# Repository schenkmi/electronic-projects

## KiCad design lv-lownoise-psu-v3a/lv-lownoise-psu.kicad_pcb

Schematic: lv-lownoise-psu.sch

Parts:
C1, C2: 100u; CP_Elec_8x6.9
C3, C4: 4.7u; C_1206_3216Metric_Pad1.33x1.80mm_HandSolder
C5, C6: 0.47u; C_0805_2012Metric_Pad1.18x1.45mm_HandSolder
C7, C9: 10u; C_1210_3225Metric_Pad1.33x2.70mm_HandSolder
C8, C10: 330nF; C_0805_2012Metric_Pad1.18x1.45mm_HandSolder
C11, C12: 100nF; C_0805_2012Metric_Pad1.18x1.45mm_HandSolder
C13, C14: 47uF; CP_Elec_6.3x5.8
D1: MB4S; TO-269AA
H1, H2, H3, H4: MountingHole; MountingHole_3.2mm_M3
J1, J3: AC; Pin_D1.3mm_L11.0mm
J2, J5, J8, J10, J11: GND; Pin_D1.3mm_L11.0mm
J4: +15V; Pin_D1.3mm_L11.0mm
J6: -15V; Pin_D1.3mm_L11.0mm
J7: LED; Pin_D1.3mm_L11.0mm
J9: +5V; Pin_D1.3mm_L11.0mm
J12: -5V; Pin_D1.3mm_L11.0mm
Q1: BD679; TO-126-3_Vertical
Q2: BD680; TO-126-3_Vertical
R1, R2: 150k; R_0805_2012Metric_Pad1.20x1.40mm_HandSolder
R3: 240R; R_0805_2012Metric_Pad1.20x1.40mm_HandSolder
R5, R6, R7, R8: 15k; R_0805_2012Metric_Pad1.20x1.40mm_HandSolder
RV1, RV2: 200k; Potentiometer_Bourns_3296W_Vertical
U1: L78L05_SOT89; SOT-89-3
U2: L79L05_SOT89; SOT-89-3
U3: LT3045xMSE; MSOP-12-1EP_3x4mm_P0.65mm_EP1.65x2.85mm
U4: LT3094xMSE; MSOP-12-1EP_3x4mm_P0.65mm_EP1.65x2.85mm

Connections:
GND: C1.2, C2.1, C3.2, C4.1, C5.2, C6.1, C7.1, C8.2, C9.2, C10.1, C11.2, C12.1, C13.2, C14.1, J2.1, J5.1, J8.1, J10.1, J11.1, R1.2, R2.1, R6.2, R7.1, RV1.2, RV1.3, RV2.2, RV2.3, U1.2, U2.1, U3.6 (ILIM), U3.9 (GND), U3.13 (GND), U4.6 (ILIM), U4.9 (GND)
unnamed: C1.1, C8.1, D1.3 (+), Q1.2 (C), R5.1, U1.3
unnamed: C3.1, Q1.1 (E), U3.1 (IN), U3.2 (IN), U3.3 (IN), U3.4 (EN/UV), U3.7 (PGFB)
unnamed: C4.2, Q2.1 (E), U4.1 (IN), U4.2 (IN), U4.3 (EN/UV), U4.5 (PGFB), U4.13 (IN)
unnamed: C5.1, R1.1, RV1.1, U3.8 (SET)
unnamed: C6.2, R2.2, RV2.1, U4.8 (SET)
unnamed: C7.2, J6.1, U4.10 (OUTS), U4.11 (OUT), U4.12 (OUT)
unnamed: C9.1, J4.1, U3.10 (OUTS), U3.11 (OUT), U3.12 (OUT)
unnamed: C2.2, C10.2, D1.4 (-), Q2.2 (C), R8.2, U2.2
unnamed: C11.1, C13.1, J9.1, R3.2, U1.1
unnamed: C12.2, C14.2, J12.1, U2.3
unnamed: D1.1 (~~), J3.1
unnamed: D1.2 (~~), J1.1
unnamed: J7.1, R3.1
unnamed: Q1.3 (B), R5.2, R6.1
unnamed: Q2.3 (B), R7.2, R8.1

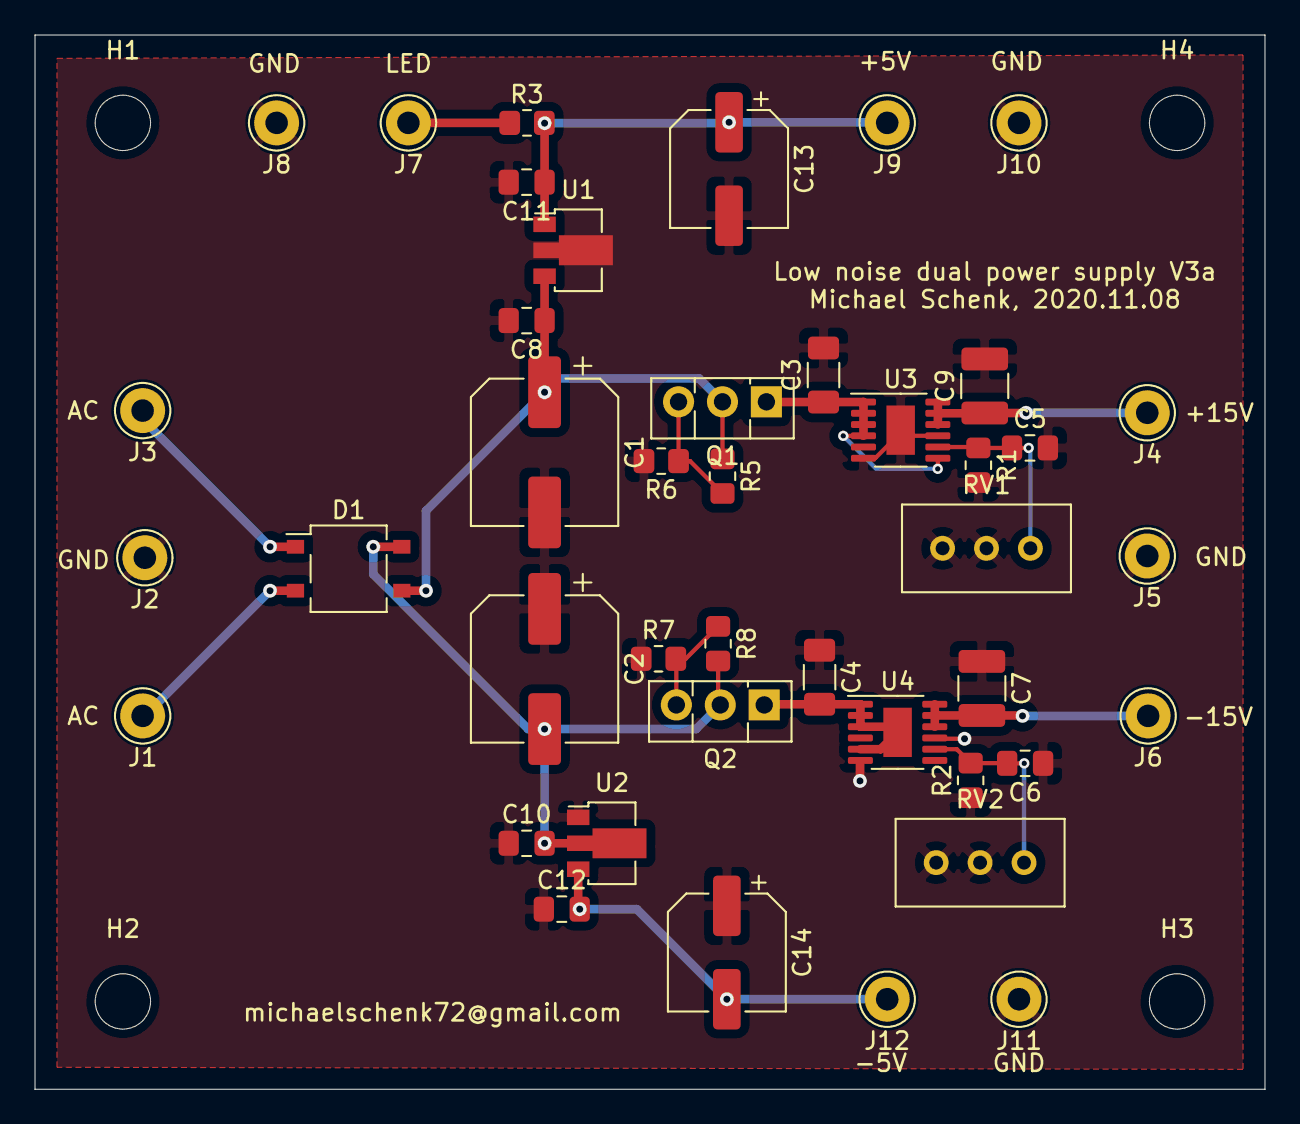
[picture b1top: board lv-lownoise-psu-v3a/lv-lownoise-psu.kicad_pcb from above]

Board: 2 copper layers, 71.1 x 61.0 mm, 46 parts (0 on the bottom side), 16 nets.

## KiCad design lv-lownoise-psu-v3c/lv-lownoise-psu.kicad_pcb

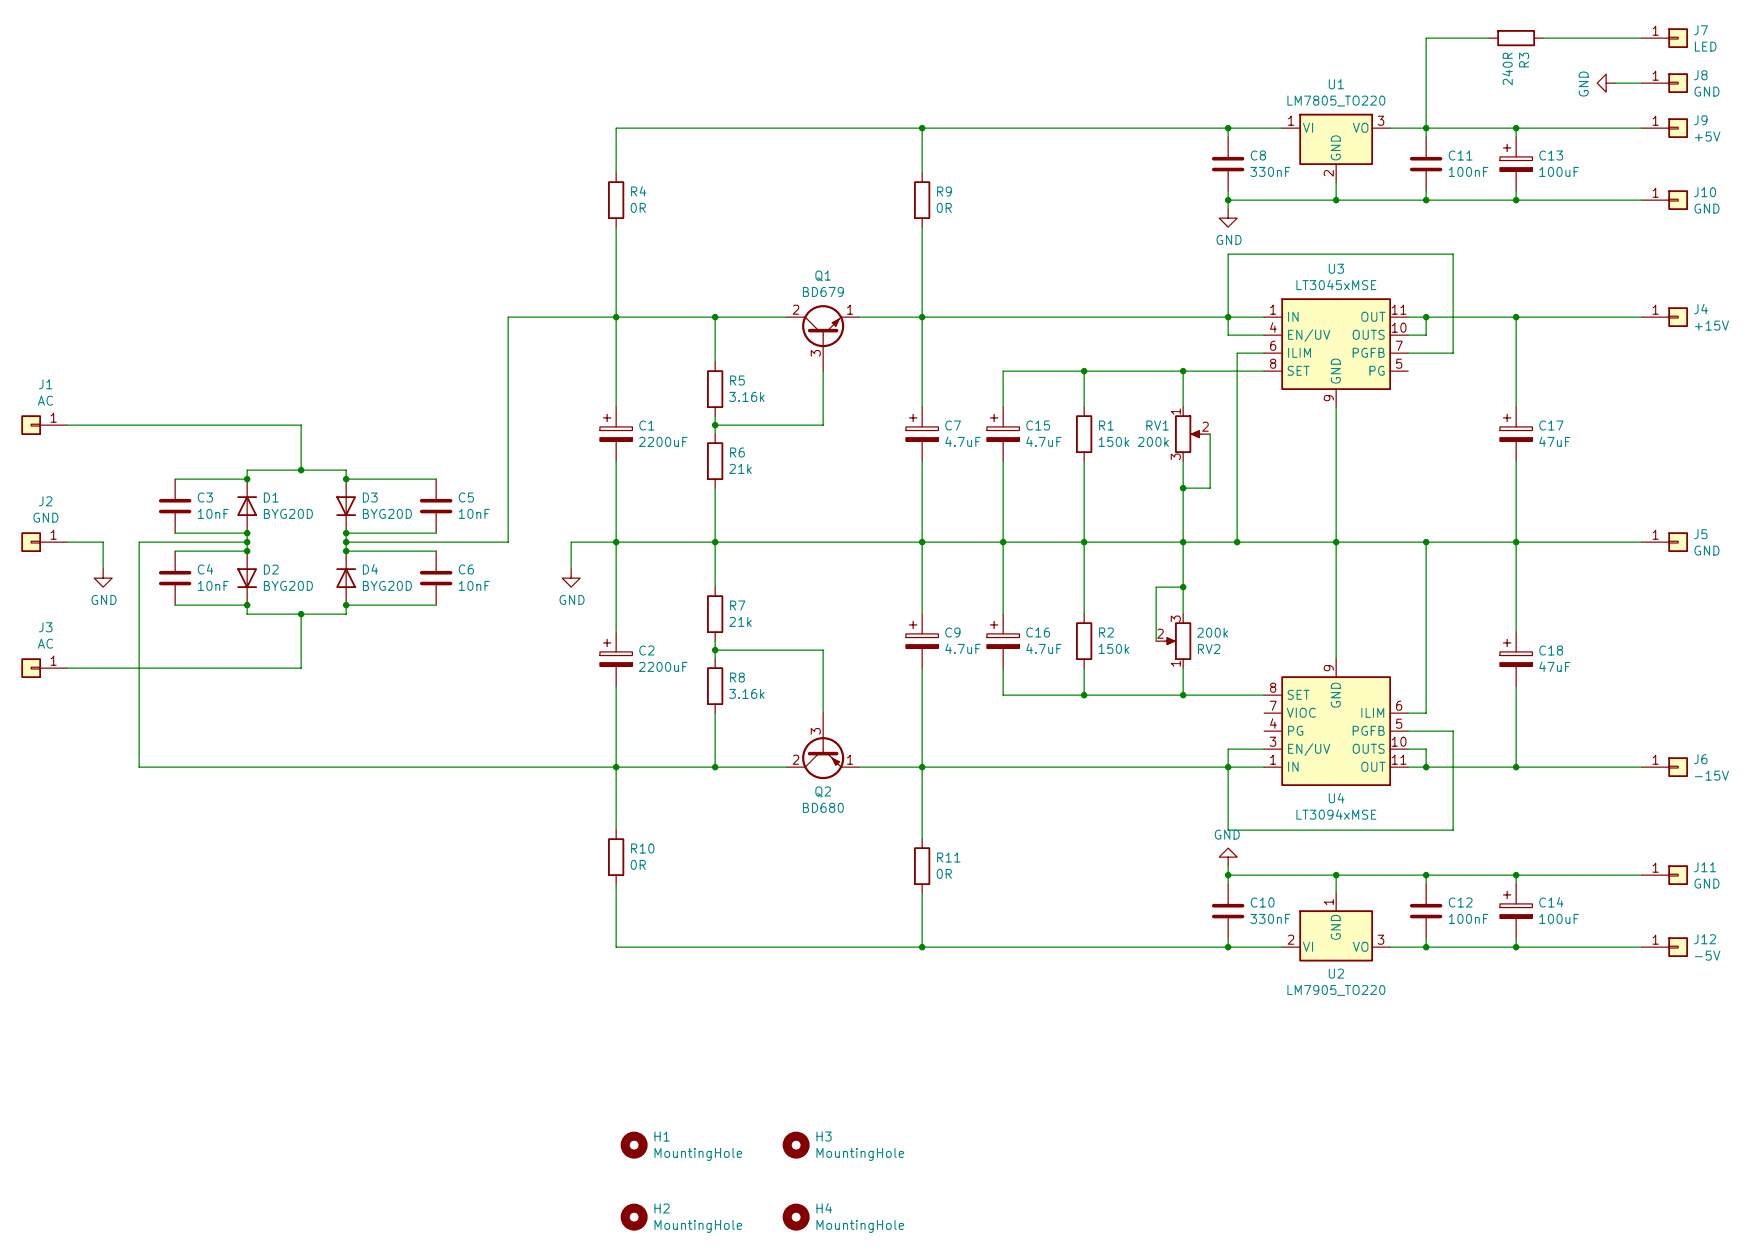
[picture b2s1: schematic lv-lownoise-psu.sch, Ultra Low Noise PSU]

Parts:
C1, C2: 2200uF; CP_Radial_D16.0mm_P7.50mm
C3, C4, C5, C6: 10nF; C_0805_2012Metric_Pad1.18x1.45mm_HandSolder
C7, C9, C15, C16: 4.7uF; CP_EIA-2012-12_Kemet-R_Pad1.30x1.05mm_HandSolder
C8, C10: 330nF; C_0805_2012Metric_Pad1.18x1.45mm_HandSolder
C11, C12: 100nF; C_0805_2012Metric_Pad1.18x1.45mm_HandSolder
C13, C14: 100uF; CP_Radial_D8.0mm_P3.50mm
C17, C18: 47uF; CP_EIA-7343-31_Kemet-D_Pad2.25x2.55mm_HandSolder
D1, D2, D3, D4: BYG20D; D_SMA_Handsoldering
H1, H2, H3, H4: MountingHole; MountingHole_3.2mm_M3
J1, J3: AC; Pin_D1.3mm_L11.0mm
J2, J5, J8, J10, J11: GND; Pin_D1.3mm_L11.0mm
J4: +15V; Pin_D1.3mm_L11.0mm
J6: -15V; Pin_D1.3mm_L11.0mm
J7: LED; Pin_D1.3mm_L11.0mm
J9: +5V; Pin_D1.3mm_L11.0mm
J12: -5V; Pin_D1.3mm_L11.0mm
Q1: BD679; TO-126-3_Vertical
Q2: BD680; TO-126-3_Vertical
R1, R2: 150k; R_0805_2012Metric_Pad1.20x1.40mm_HandSolder
R3: 240R; R_0805_2012Metric_Pad1.20x1.40mm_HandSolder
R4, R9, R10, R11: 0R; R_0805_2012Metric_Pad1.15x1.40mm_HandSolder
R5, R8: 3.16k; R_0805_2012Metric_Pad1.20x1.40mm_HandSolder
R6, R7: 21k; R_0805_2012Metric_Pad1.20x1.40mm_HandSolder
RV1, RV2: 200k; Potentiometer_Bourns_3296W_Vertical
U1: LM7805_TO220; TO-220-3_Vertical
U2: LM7905_TO220; TO-220-3_Vertical
U3: LT3045xMSE; MSOP-12-1EP_3x4mm_P0.65mm_EP1.65x2.85mm
U4: LT3094xMSE; MSOP-12-1EP_3x4mm_P0.65mm_EP1.65x2.85mm

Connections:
GND: C1.2, C2.1, C7.2, C8.2, C9.1, C10.1, C11.2, C12.1, C13.2, C14.1, C15.2, C16.1, C17.2, C18.1, J2.1, J5.1, J8.1, J10.1, J11.1, R1.2, R2.1, R6.2, R7.1, RV1.2, RV1.3, RV2.2, RV2.3, U1.2 (GND), U2.1 (GND), U3.6 (ILIM), U3.9 (GND), U3.13 (GND), U4.6 (ILIM), U4.9 (GND)
unnamed: C1.1, C5.2, C6.1, D3.1 (K), D4.1 (K), Q1.2 (C), R4.2, R5.1
unnamed: C2.2, C3.2, C4.1, D1.2 (A), D2.2 (A), Q2.2 (C), R8.2, R10.1
unnamed: C3.1, C5.1, D1.1 (K), D3.2 (A), J1.1
unnamed: C4.2, C6.2, D2.1 (K), D4.2 (A), J3.1
unnamed: C7.1, Q1.1 (E), R9.2, U3.1 (IN), U3.2 (IN), U3.3 (IN), U3.4 (EN/UV), U3.7 (PGFB)
unnamed: C8.1, R4.1, R9.1, U1.1 (VI)
unnamed: C9.2, Q2.1 (E), R11.1, U4.1 (IN), U4.2 (IN), U4.3 (EN/UV), U4.5 (PGFB), U4.13 (IN)
unnamed: C10.2, R10.2, R11.2, U2.2 (VI)
unnamed: C11.1, C13.1, J9.1, R3.2, U1.3 (VO)
unnamed: C12.2, C14.2, J12.1, U2.3 (VO)
unnamed: C15.1, R1.1, RV1.1, U3.8 (SET)
unnamed: C16.2, R2.2, RV2.1, U4.8 (SET)
unnamed: C17.1, J4.1, U3.10 (OUTS), U3.11 (OUT), U3.12 (OUT)
unnamed: C18.2, J6.1, U4.10 (OUTS), U4.11 (OUT), U4.12 (OUT)
unnamed: J7.1, R3.1
unnamed: Q1.3 (B), R5.2, R6.1
unnamed: Q2.3 (B), R7.2, R8.1

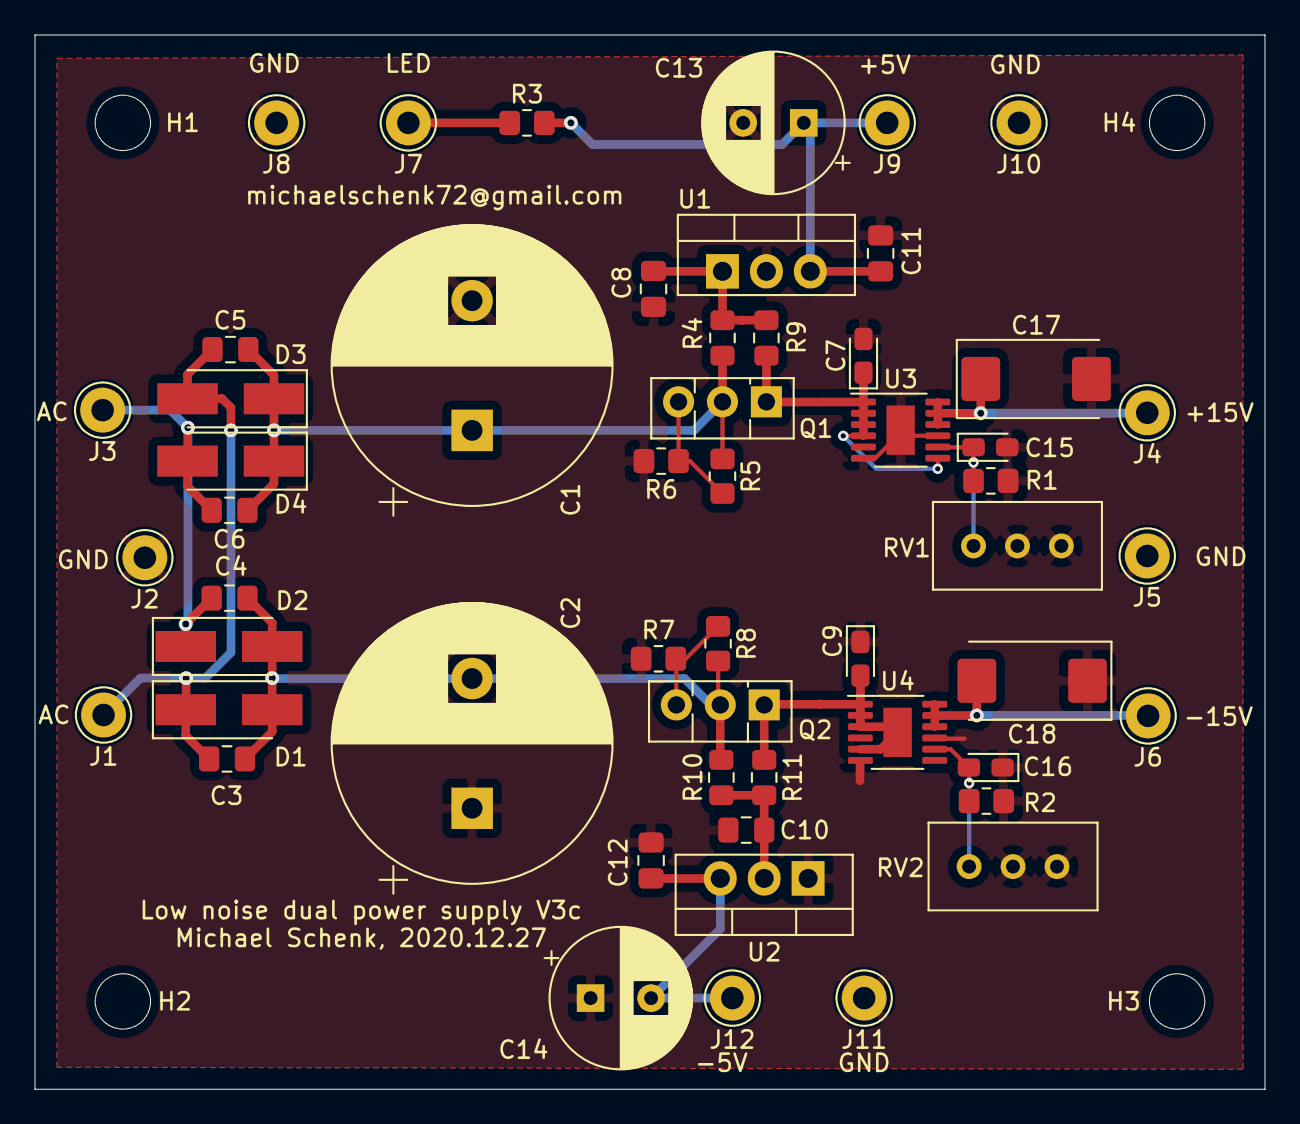
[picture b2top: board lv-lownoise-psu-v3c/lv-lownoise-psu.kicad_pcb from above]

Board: 2 copper layers, 71.1 x 61.0 mm, 57 parts (0 on the bottom side), 18 nets.

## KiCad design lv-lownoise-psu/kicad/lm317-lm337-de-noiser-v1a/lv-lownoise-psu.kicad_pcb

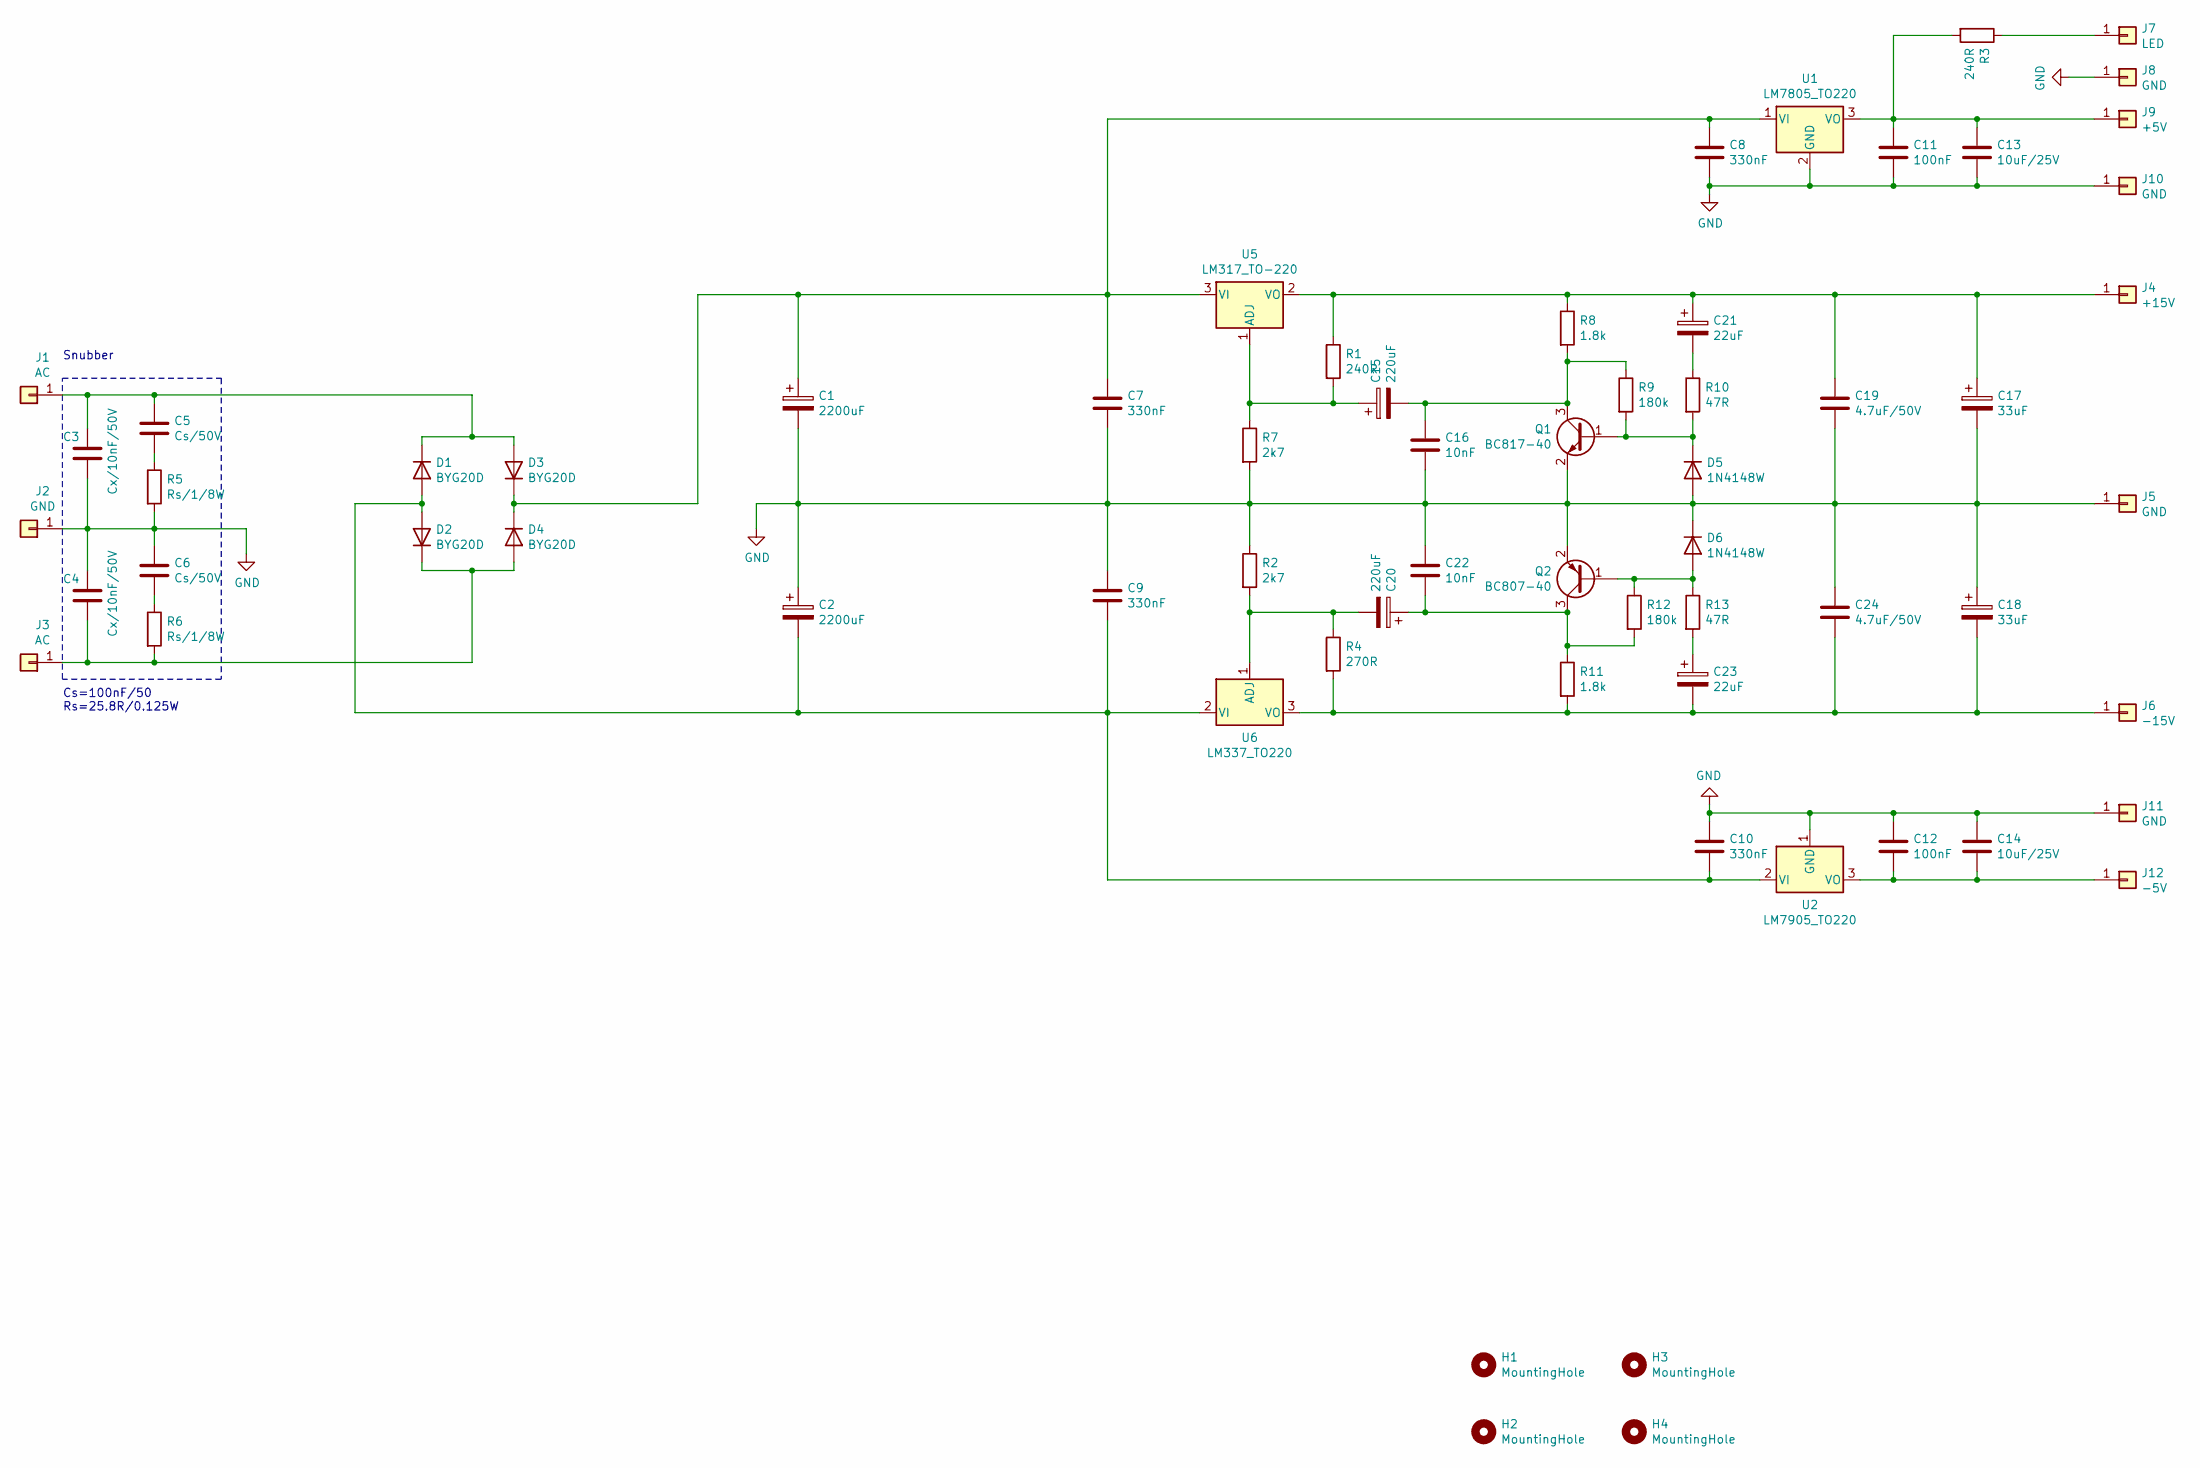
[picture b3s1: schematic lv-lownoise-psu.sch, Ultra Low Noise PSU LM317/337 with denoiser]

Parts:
C1, C2: 2200uF; CP_Radial_D16.0mm_P7.50mm
C3, C4: Cx/10nF/50V; C_0805_2012Metric_Pad1.18x1.45mm_HandSolder
C5, C6: Cs/50V; C_0805_2012Metric_Pad1.18x1.45mm_HandSolder
C7, C8, C9, C10: 330nF; C_0805_2012Metric_Pad1.18x1.45mm_HandSolder
C11, C12: 100nF; C_0805_2012Metric_Pad1.18x1.45mm_HandSolder
C13, C14: 10uF/25V; C_1206_3216Metric_Pad1.33x1.80mm_HandSolder
C15, C20: 220uF; CP_Radial_D8.0mm_P5.00mm
C16, C22: 10nF; C_0805_2012Metric_Pad1.18x1.45mm_HandSolder
C17, C18: 33uF; CP_EIA-7343-31_Kemet-D_Pad2.25x2.55mm_HandSolder
C19, C24: 4.7uF/50V; C_1206_3216Metric_Pad1.33x1.80mm_HandSolder
C21, C23: 22uF; CP_Radial_D5.0mm_P2.50mm
D1, D2, D3, D4: BYG20D; D_SMA_Handsoldering
D5, D6: 1N4148W; D_SOD-123
H1, H2, H3, H4: MountingHole; MountingHole_3.2mm_M3
J1, J3: AC; Pin_D1.3mm_L11.0mm
J2: GND; Pin_D1.3mm_L11.0mm
J4: +15V; Pin_D1.0mm_L10.0mm
J5, J8, J10, J11: GND; Pin_D1.0mm_L10.0mm
J6: -15V; Pin_D1.0mm_L10.0mm
J7: LED; Pin_D1.0mm_L10.0mm
J9: +5V; Pin_D1.0mm_L10.0mm
J12: -5V; Pin_D1.0mm_L10.0mm
Q1: BC817-40; SOT-23
Q2: BC807-40; SOT-23
R1, R3: 240R; R_0805_2012Metric_Pad1.20x1.40mm_HandSolder
R2, R7: 2k7; R_0805_2012Metric_Pad1.20x1.40mm_HandSolder
R4: 270R; R_0805_2012Metric_Pad1.20x1.40mm_HandSolder
R5, R6: Rs/1/8W; R_0805_2012Metric_Pad1.20x1.40mm_HandSolder
R8, R11: 1.8k; R_0805_2012Metric_Pad1.20x1.40mm_HandSolder
R9, R12: 180k; R_0805_2012Metric_Pad1.20x1.40mm_HandSolder
R10, R13: 47R; R_0805_2012Metric_Pad1.20x1.40mm_HandSolder
U1: LM7805_TO220; TO-220-3_Vertical
U2: LM7905_TO220; TO-220-3_Vertical
U5: LM317_TO-220; TO-220-3_Vertical
U6: LM337_TO220; TO-220-3_Vertical

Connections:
GND: C1.2, C2.1, C3.2, C4.1, C6.1, C7.2, C8.2, C9.1, C10.1, C11.2, C12.1, C13.2, C14.1, C16.2, C17.2, C18.1, C19.2, C22.1, C24.1, D5.2 (A), D6.1 (K), J2.1, J5.1, J8.1, J10.1, J11.1, Q1.2 (E), Q2.2 (E), R2.1, R5.2, R7.2, U1.2 (GND), U2.1 (GND)
unnamed: C1.1, C7.1, C8.1, D3.1 (K), D4.1 (K), U1.1 (VI), U5.3 (VI)
unnamed: C3.1, C5.1, D1.1 (K), D3.2 (A), J1.1
unnamed: C4.2, D2.1 (K), D4.2 (A), J3.1, R6.2
unnamed: C5.2, R5.1
unnamed: C6.2, R6.1
unnamed: C2.2, C9.2, C10.2, D1.2 (A), D2.2 (A), U2.2 (VI), U6.2 (VI)
unnamed: C11.1, C13.1, J9.1, R3.2, U1.3 (VO)
unnamed: C12.2, C14.2, J12.1, U2.3 (VO)
unnamed: C15.1, R1.2, R7.1, U5.1 (ADJ)
unnamed: C15.2, C16.1, Q1.3 (C), R8.2, R9.1
unnamed: C17.1, C19.1, C21.1, J4.1, R1.1, R8.1, U5.2 (VO)
unnamed: C18.2, C23.2, C24.2, J6.1, R4.2, R11.2, U6.3 (VO)
unnamed: C20.1, C22.2, Q2.3 (C), R11.1, R12.2
unnamed: C20.2, R2.2, R4.1, U6.1 (ADJ)
unnamed: C21.2, R10.1
unnamed: C23.1, R13.2
unnamed: D5.1 (K), Q1.1 (B), R9.2, R10.2
unnamed: D6.2 (A), Q2.1 (B), R12.1, R13.1
unnamed: J7.1, R3.1

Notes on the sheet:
Snubber
Cs=100nF/50 Rs=25.8R/0.125W

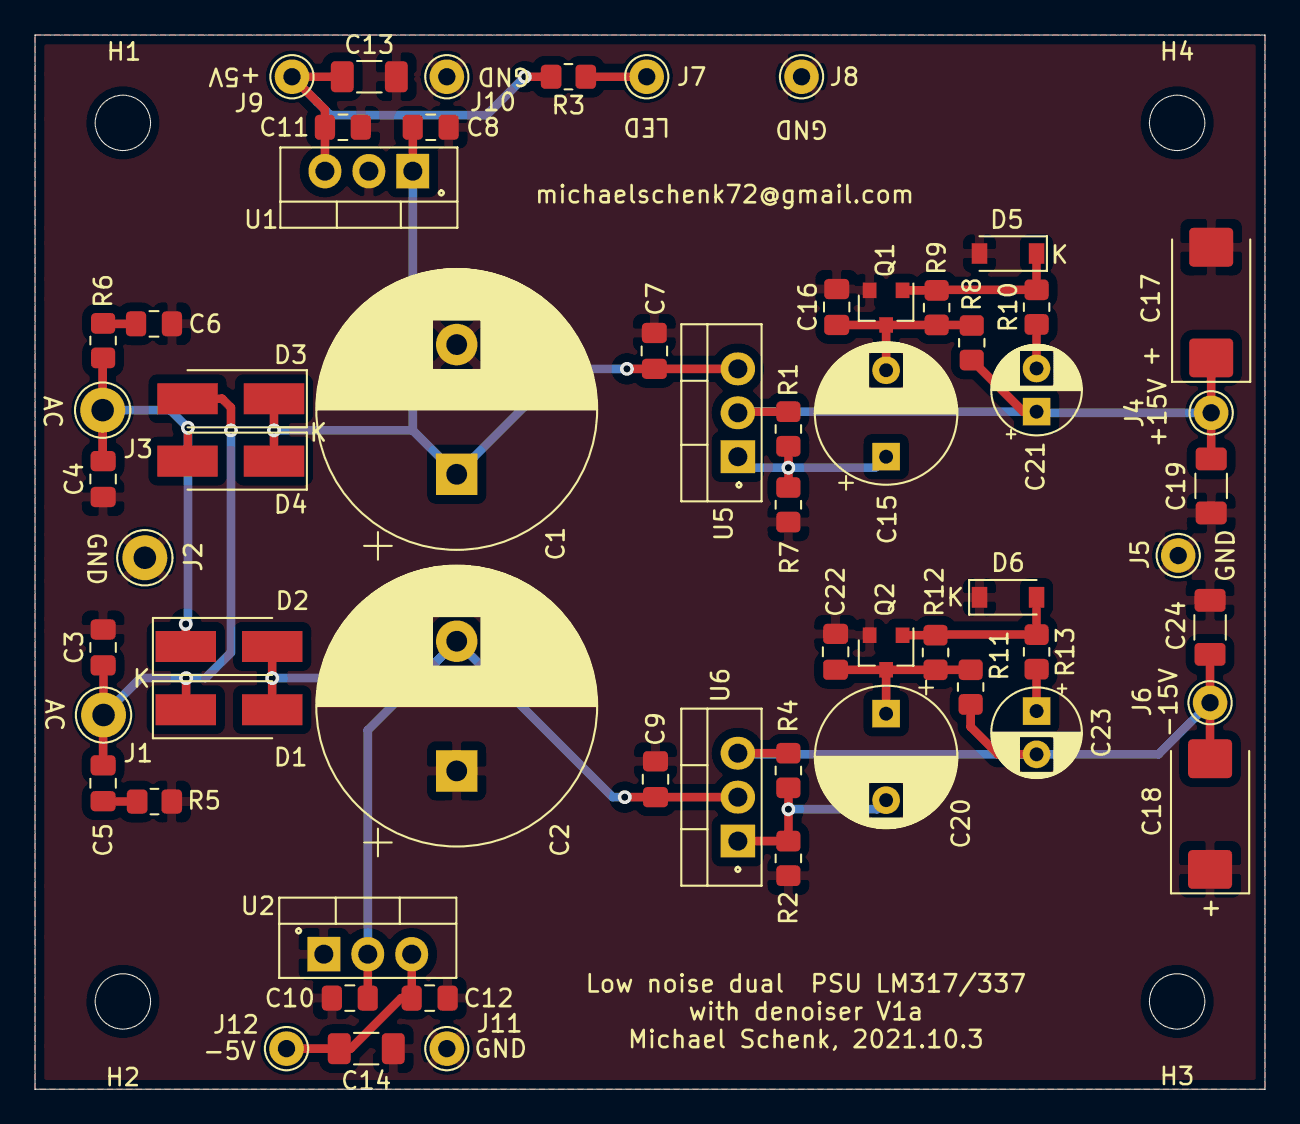
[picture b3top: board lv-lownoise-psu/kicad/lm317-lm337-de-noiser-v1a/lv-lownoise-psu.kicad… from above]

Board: 2 copper layers, 71.1 x 61.0 mm, 65 parts (0 on the bottom side), 20 nets.

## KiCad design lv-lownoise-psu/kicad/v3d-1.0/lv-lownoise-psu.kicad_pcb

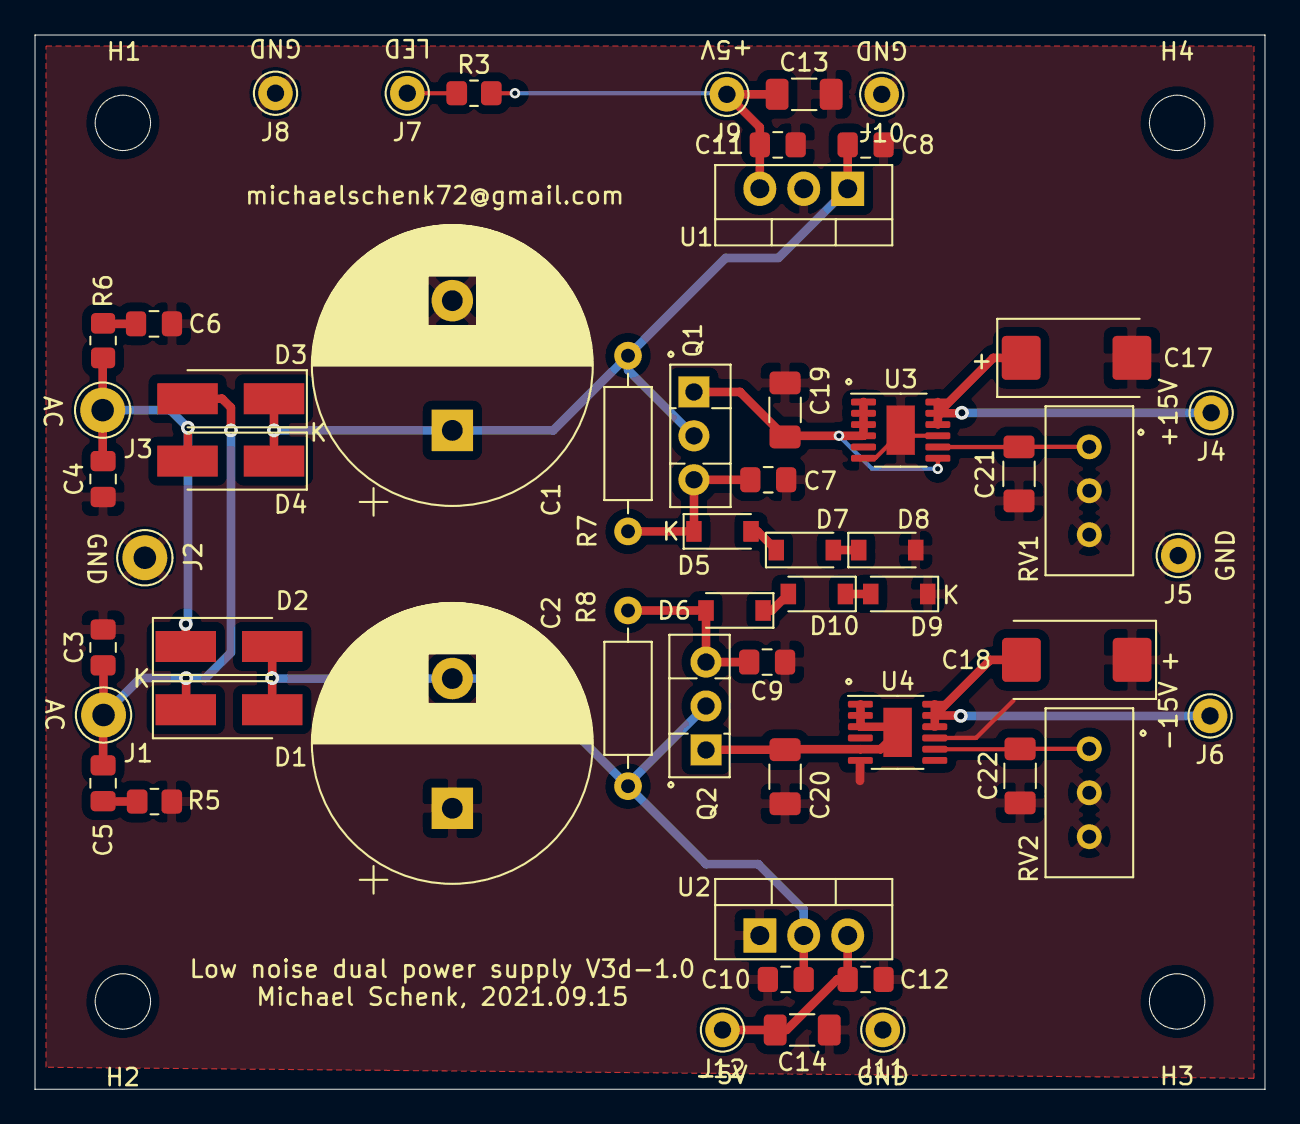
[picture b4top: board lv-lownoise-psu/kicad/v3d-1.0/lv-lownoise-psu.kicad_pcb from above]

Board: 2 copper layers, 71.1 x 61.0 mm, 59 parts (0 on the bottom side), 22 nets.

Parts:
C1, C2: 2200uF; CP_Radial_D16.0mm_P7.50mm
C3, C4: Cx/10nF/50V; C_0805_2012Metric_Pad1.18x1.45mm_HandSolder
C5, C6: Cs/50V; C_0805_2012Metric_Pad1.18x1.45mm_HandSolder
C7, C9, C11, C12: 100nF; C_0805_2012Metric_Pad1.18x1.45mm_HandSolder
C8, C10: 330nF; C_0805_2012Metric_Pad1.18x1.45mm_HandSolder
C13, C14: 10uF/25V; C_1206_3216Metric_Pad1.33x1.80mm_HandSolder
C17, C18: 33uF; CP_EIA-7343-31_Kemet-D_Pad2.25x2.55mm_HandSolder
C19, C20, C21, C22: 4.7uF/25V; C_1206_3216Metric_Pad1.33x1.80mm_HandSolder
D1, D2, D3, D4: BYG20D; D_SMA_Handsoldering
D5, D6, D7, D8, D9, D10: MMSZ5232B/5.6V; D_SOD-123
H1, H2, H3, H4: MountingHole; MountingHole_3.2mm_M3
J1, J3: AC; Pin_D1.3mm_L11.0mm
J2: GND; Pin_D1.3mm_L11.0mm
J4: +15V; Pin_D1.0mm_L10.0mm
J5, J8, J10, J11: GND; Pin_D1.0mm_L10.0mm
J6: -15V; Pin_D1.0mm_L10.0mm
J7: LED; Pin_D1.0mm_L10.0mm
J9: +5V; Pin_D1.0mm_L10.0mm
J12: -5V; Pin_D1.0mm_L10.0mm
Q1: BD139; TO-126-3_Vertical
Q2: BD140; TO-126-3_Vertical
R3: 240R; R_0805_2012Metric_Pad1.20x1.40mm_HandSolder
R5, R6: Rs/1/8W; R_0805_2012Metric_Pad1.20x1.40mm_HandSolder
R7, R8: 430R/0.6W; R_Axial_DIN0207_L6.3mm_D2.5mm_P10.16mm_Horizontal
RV1, RV2: 200k; Potentiometer_Bourns_3296W_Vertical
U1: LM7805_TO220; TO-220-3_Vertical
U2: LM7905_TO220; TO-220-3_Vertical
U3: LT3045xMSE; MSOP-12-1EP_3x4mm_P0.65mm_EP1.65x2.85mm
U4: LT3094xMSE; MSOP-12-1EP_3x4mm_P0.65mm_EP1.65x2.85mm

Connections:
GND: C1.2, C2.1, C3.2, C4.1, C6.1, C7.2, C8.2, C9.1, C10.1, C11.2, C12.1, C13.2, C14.1, C17.2, C18.1, C19.2, C20.1, C21.2, C22.1, D8.2, D9.1, J2.1, J5.1, J8.1, J10.1, J11.1, R5.2, RV1.2, RV1.3, RV2.2, RV2.3, U1.2, U2.1, U3.6, U3.9, U3.13, U4.6, U4.9
unnamed: C1.1, C8.1, D3.1, D4.1, Q1.2, R7.1, U1.1
unnamed: C3.1, C5.1, D1.1, D3.2, J1.1
unnamed: C4.2, D2.1, D4.2, J3.1, R6.2
unnamed: C5.2, R5.1
unnamed: C6.2, R6.1
unnamed: C7.1, D5.1, Q1.3, R7.2
unnamed: C9.2, D6.2, Q2.3, R8.1
unnamed: C2.2, C10.2, D1.2, D2.2, Q2.2, R8.2, U2.2
unnamed: C11.1, C13.1, J9.1, R3.2, U1.3
unnamed: C12.2, C14.2, J12.1, U2.3
unnamed: C17.1, J4.1, U3.10, U3.11, U3.12
unnamed: C18.2, J6.1, U4.10, U4.11, U4.12
unnamed: C19.1, Q1.1, U3.1, U3.2, U3.3, U3.4, U3.7
unnamed: C20.2, Q2.1, U4.1, U4.2, U4.3, U4.5, U4.13
unnamed: C21.1, RV1.1, U3.8
unnamed: C22.2, RV2.1, U4.8
unnamed: D5.2, D7.1
unnamed: D7.2, D8.1
unnamed: D9.2, D10.1
unnamed: D6.1, D10.2
unnamed: J7.1, R3.1
